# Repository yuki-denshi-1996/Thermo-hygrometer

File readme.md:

## はじめに
このプロジェクトは、温湿度計を基板設計から作ろうという計画です。  
詳しくは下のブログを御覧ください。  
https://denshi1996.sub.jp/2024/04/%e6%99%82%e8%a8%88%e6%a9%9f%e8%83%bd%e4%bb%98%e3%81%8d%e6%b8%a9%e6%b9%bf%e5%ba%a6%e8%a8%88%e3%82%92%e4%bd%9c%e3%82%8d%e3%81%86%e3%80%80%e7%9b%ae%e6%ac%a1/

## 回路設計
回路設計データは temp_monitor ディレクトリに入っています。  
KiCad 8.0で作成しています。なお、一部雑な部分があります。ご了承ください。  
なお、フットプリントは配布していません。ご了承ください。

## プログラムソース
準備中

## 再利用等について
もともと、GitHubにバックアップとして上げているものです。自由にお使いください。  
（個人で使うなら、いろいろ修正したほうが良いと思います）

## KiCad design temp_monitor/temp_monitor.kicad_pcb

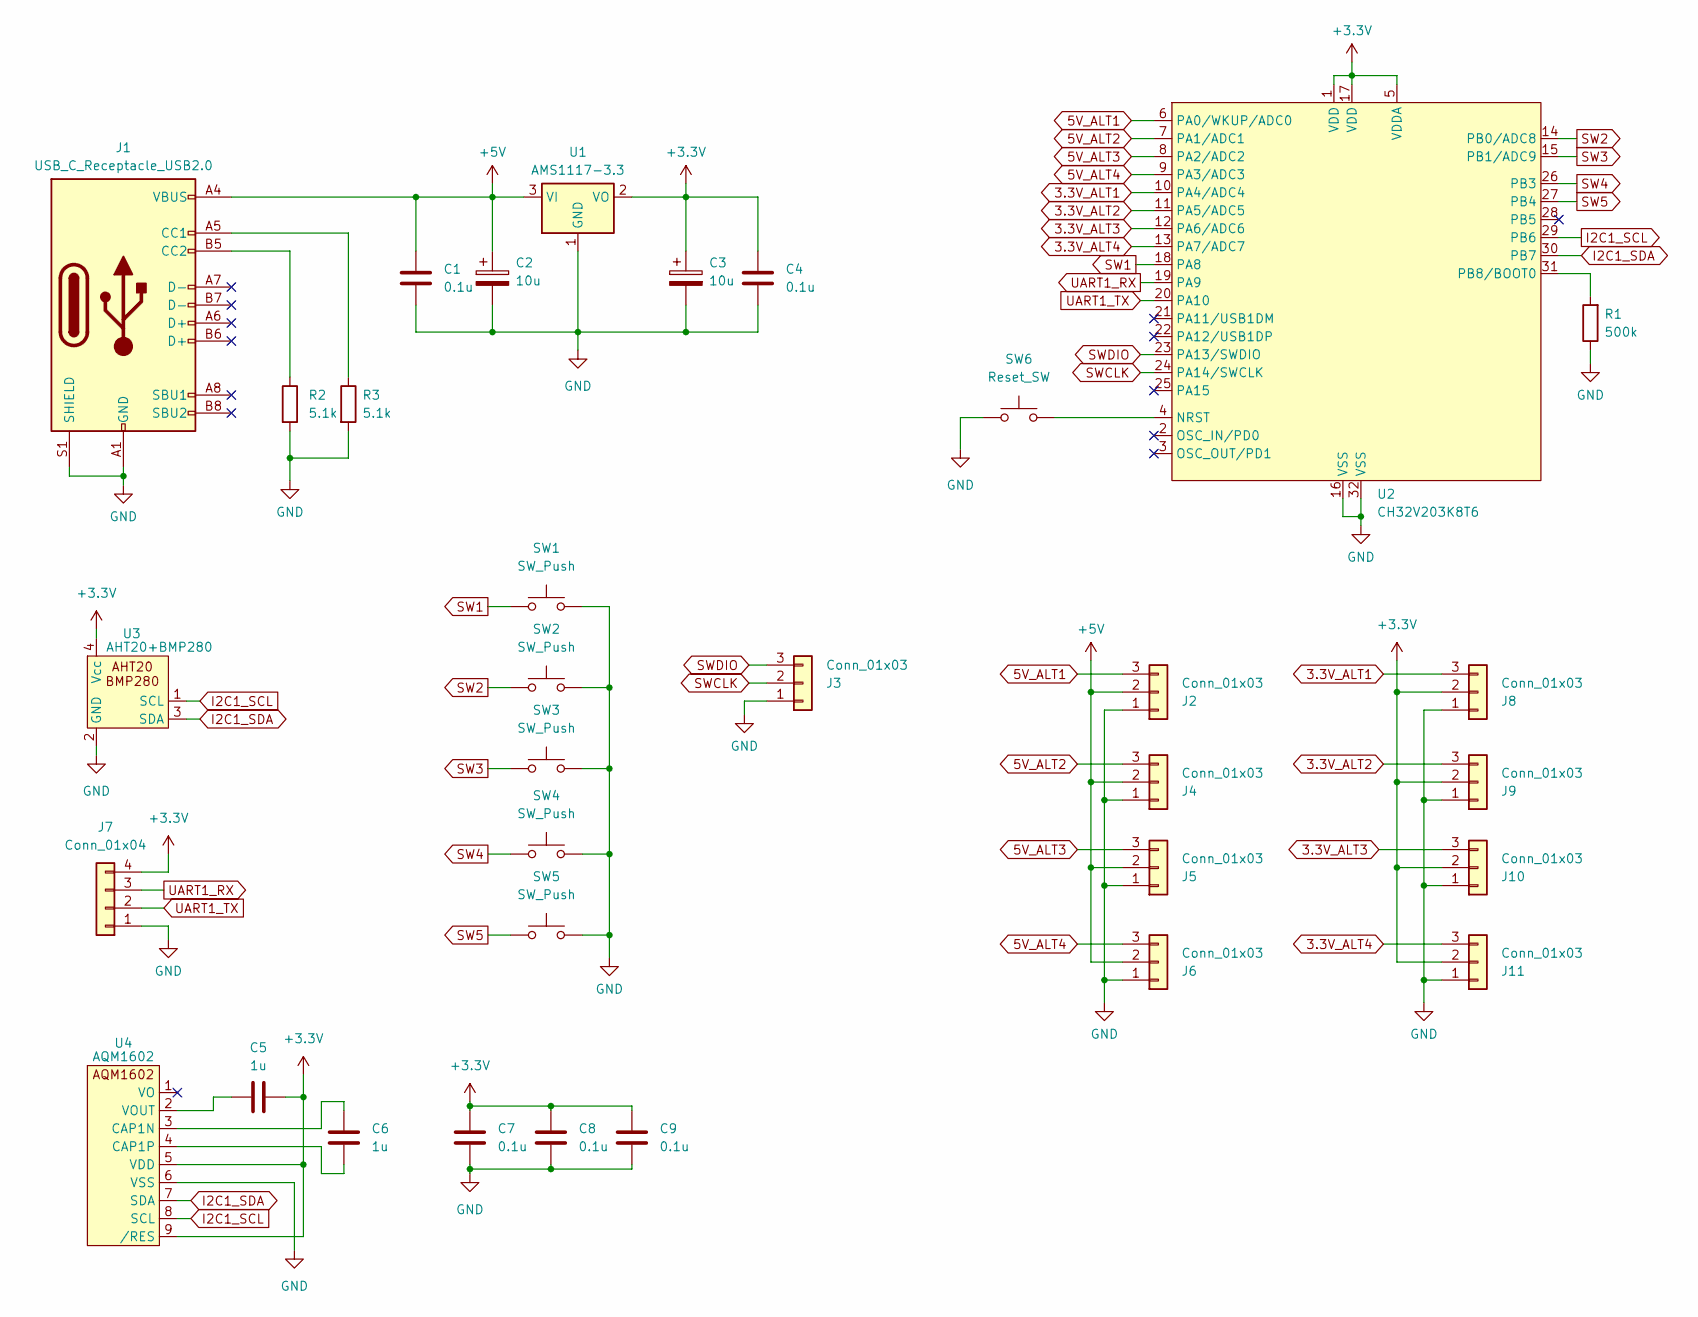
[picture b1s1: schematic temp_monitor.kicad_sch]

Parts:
C1, C4, C7, C8, C9: 0.1u; C_0603_1608Metric_Pad1.08x0.95mm_HandSolder
C2, C3: 10u; CP_Elec_4x5.4
C5, C6: 1u; C_0603_1608Metric_Pad1.08x0.95mm_HandSolder
J1: USB_C_Receptacle_USB2.0; USB_C_Receptacle_GCT_USB4105-xx-A_16P_TopMnt_Horizontal
J2, J3, J4, J5, J6, J8, J9, J10, J11: Conn_01x03; JST_XH_B3B-XH-A_1x03_P2.50mm_Vertical
J7: Conn_01x04; JST_XH_B4B-XH-A_1x04_P2.50mm_Vertical
R1: 500k; R_0603_1608Metric_Pad0.98x0.95mm_HandSolder
R2, R3: 5.1k; R_0603_1608Metric_Pad0.98x0.95mm_HandSolder
SW1, SW2, SW3, SW4, SW5: SW_Push; SW_TSB008A2518A
SW6: Reset_SW; SW_TSB008A2518A
U1: AMS1117-3.3; SOT-223-3_TabPin2
U2: CH32V203K8T6; LQFP-32_7x7mm_P0.8mm
U3: AHT20+BMP280; AHT20+BMP280_Sensor_SimpleRobot
U4: AQM1602; AQM1602Y-RN

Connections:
3.3V_ALT1: J8.3, U2.10 (PA4/ADC4)
3.3V_ALT2: J9.3, U2.11 (PA5/ADC5)
3.3V_ALT3: J10.3, U2.12 (PA6/ADC6)
3.3V_ALT4: J11.3, U2.13 (PA7/ADC7)
5V_ALT1: J2.3, U2.6 (PA0/WKUP/ADC0)
5V_ALT2: J4.3, U2.7 (PA1/ADC1)
5V_ALT3: J5.3, U2.8 (PA2/ADC2)
5V_ALT4: J6.3, U2.9 (PA3/ADC3)
+3.3V: C3.1, C4.1, C5.2, C7.2, C8.2, C9.2, J7.4, J8.2, J9.2, J10.2, J11.2, U1.2 (VO), U2.1 (VDD), U2.5 (VDDA), U2.17 (VDD), U3.4 (Vcc), U4.5 (VDD), U4.9 (/RES)
+5V: C1.1, C2.1, J1.A4 (VBUS), J1.A9 (VBUS), J1.B4 (VBUS), J1.B9 (VBUS), J2.2, J4.2, J5.2, J6.2, U1.3 (VI)
GND: C1.2, C2.2, C3.2, C4.2, C7.1, C8.1, C9.1, J1.A1 (GND), J1.A12 (GND), J1.B1 (GND), J1.B12 (GND), J1.S1 (SHIELD), J2.1, J3.1, J4.1, J5.1, J6.1, J7.1, J8.1, J9.1, J10.1, J11.1, R1.1, R2.2, R3.2, SW1.2, SW2.2, SW3.2, SW4.2, SW5.2, SW6.1, U1.1 (GND), U2.16 (VSS), U2.32 (VSS), U3.2 (GND), U4.6 (VSS)
I2C1_SCL: U2.29 (PB6), U3.1 (SCL), U4.8 (SCL)
I2C1_SDA: U2.30 (PB7), U3.3 (SDA), U4.7 (SDA)
unnamed: J1.A5 (CC1), R3.1
unnamed: J1.B5 (CC2), R2.1
unnamed: SW6.2, U2.4 (NRST)
unnamed: R1.2, U2.31 (PB8/BOOT0)
unnamed: C6.2, U4.3 (CAP1N)
unnamed: C6.1, U4.4 (CAP1P)
unnamed: C5.1, U4.2 (VOUT)
SW1: SW1.1, U2.18 (PA8)
SW2: SW2.1, U2.14 (PB0/ADC8)
SW3: SW3.1, U2.15 (PB1/ADC9)
SW4: SW4.1, U2.26 (PB3)
SW5: SW5.1, U2.27 (PB4)
SWCLK: J3.2, U2.24 (PA14/SWCLK)
SWDIO: J3.3, U2.23 (PA13/SWDIO)
UART1_RX: J7.3, U2.19 (PA9)
UART1_TX: J7.2, U2.20 (PA10)

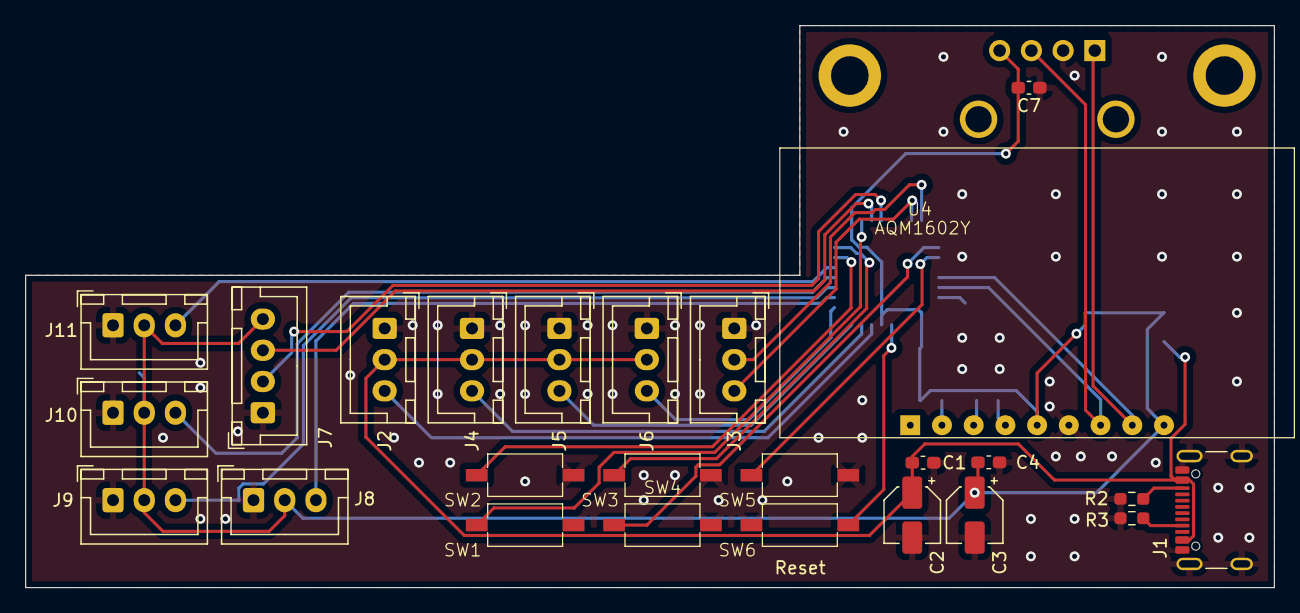
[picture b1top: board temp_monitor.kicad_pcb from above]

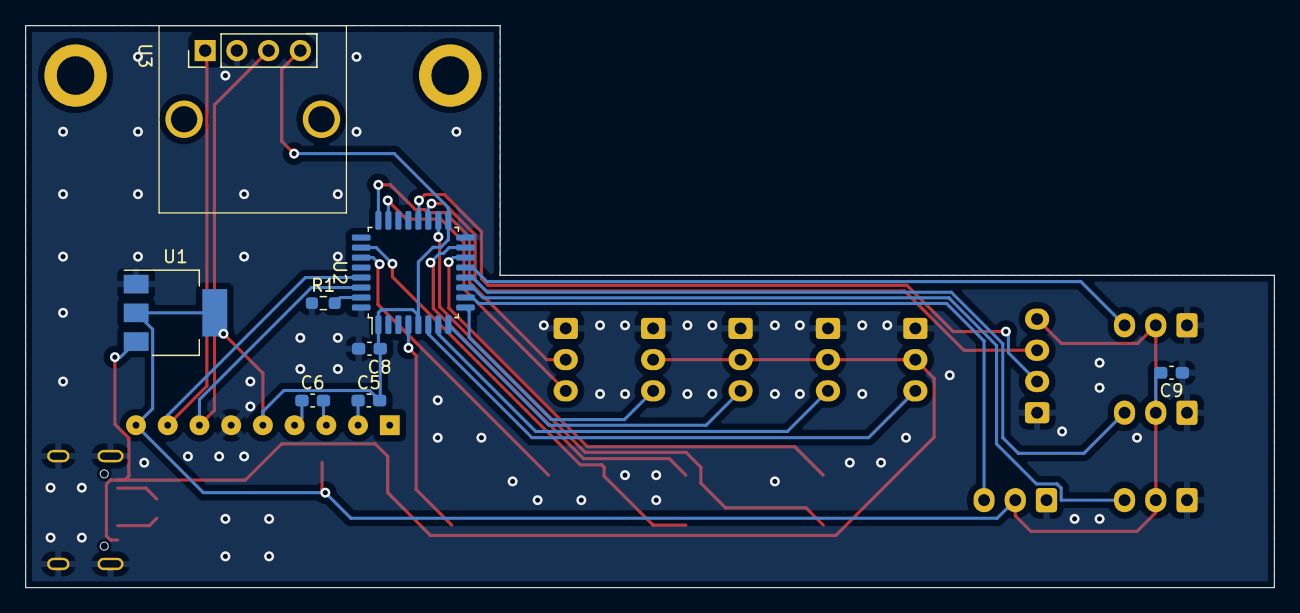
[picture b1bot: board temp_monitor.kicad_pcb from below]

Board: 2 copper layers, 100.0 x 45.0 mm, 33 parts (8 on the bottom side), 29 nets.

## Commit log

2024-04-25 Readme.mdの追加
